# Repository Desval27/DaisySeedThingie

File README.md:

# Prototyping Carrier Board for the Daisy Seed™ 

https://electro-smith.com/products/daisy-seed

This PCB is designed to breakout all the PINs of the Daisy Seed along with additional components such as push buttons, LEDs, potentiometers, I<sup>2</sup>C, and SD card interfaces along with enough room for a typical 830 point breadboard.  

All 40 Daisy PINs are available on both sides of the board with those on the left being mirrored/inverted for additional flexibility.

[Interactive Bill of Materials (BOM)](https://github.com/Desval27/DaisySeedThingie/blob/main/bom/ibom.html)

## Ready to Order Gerber Files
- [Default](hardware/gerber_to_order/DaisySeedThingie_254.0x167.64mm_for_Default.zip)
- [Elecrow](hardware/gerber_to_order/DaisySeedThingie_254.0x167.64mm_for_Elecrow.zip)
- [FusionPCB](hardware/gerber_to_order/DaisySeedThingie_254.0x167.64mm_for_FusionPCB.zip)
- [JLCPCB](hardware/gerber_to_order/DaisySeedThingie_254.0x167.64mm_for_JLCPCB.zip)
- [PCBWay](hardware/gerber_to_order/DaisySeedThingie_254.0x167.64mm_for_PCBWay.zip)

## Status

Repository updated to Revision B.  Revision B is currently being tested.

Revsion A has several issues that are being corrected in Revision B.  Revision B is close to being finished.

- Due to footprint and learning issues no 3.5mm jacks are actually connected.  They can be hacked on the backside.
- All potentiometers are wired backwards.  CCW increases the voltage at the wiper while CW decreases it.

## Notes:
- Push buttons are connected on one side to GND to be used with input pullup GPIO pins.
- Potentiomenters are prewired on on the CW & CCW sides to +3V3 and GND.
- Audio in/out jacks are directly connected to the Seed's audio in/out pins.
   If the mono audio in jacks are used left audio in is normalized to right audio in so that they will both be available for processing by the seed if nothing is connected to right audio in.
- JST connectors are provided to breakout the Audio in/out and MIDI in/out signals to external jacks (1/4" Phono, 5-pin DIN, etc.).
- Jumpers are provided to change the configuration between TRS MIDI-A and TRS MIDI-B.  The default configuration is MIDI-A.  If MIDI-B is desired then the jumpers for MIDI-A need to be cut and those for MIDI-B bridged.

## ⚠️ Disclaimer

This project is provided **"as is"**, without warranty of any kind, express or implied,
including but not limited to the warranties of merchantability, fitness for a
particular purpose, and noninfringement.

This is a DIY electronics project intended for educational and experimental use.
Use at your own risk.

The author assumes **no responsibility or liability** for any damage, injury, or loss
resulting from the use or misuse of this design, including but not limited to:

* Damage to connected equipment (Eurorack modules, power supplies, computers, etc.)
* Incorrect assembly or wiring
* Use with incompatible voltages or signal levels
* Personal injury

### Electrical Safety

This project may interface with:

* ±12V Eurorack power rails
* External control voltages (CV)
* Digital and analog circuitry

Improper handling may result in damage or unsafe conditions.

You are responsible for:

* Verifying all connections before powering the system
* Ensuring correct polarity of power connections
* Confirming voltage ranges and signal compatibility
* Using appropriate protection circuits where necessary

### No Guarantees

Schematics, PCB layouts, and code are provided for reference only.
They may contain errors, omissions, or design flaws.

**Always review and validate the design before building or using it.**

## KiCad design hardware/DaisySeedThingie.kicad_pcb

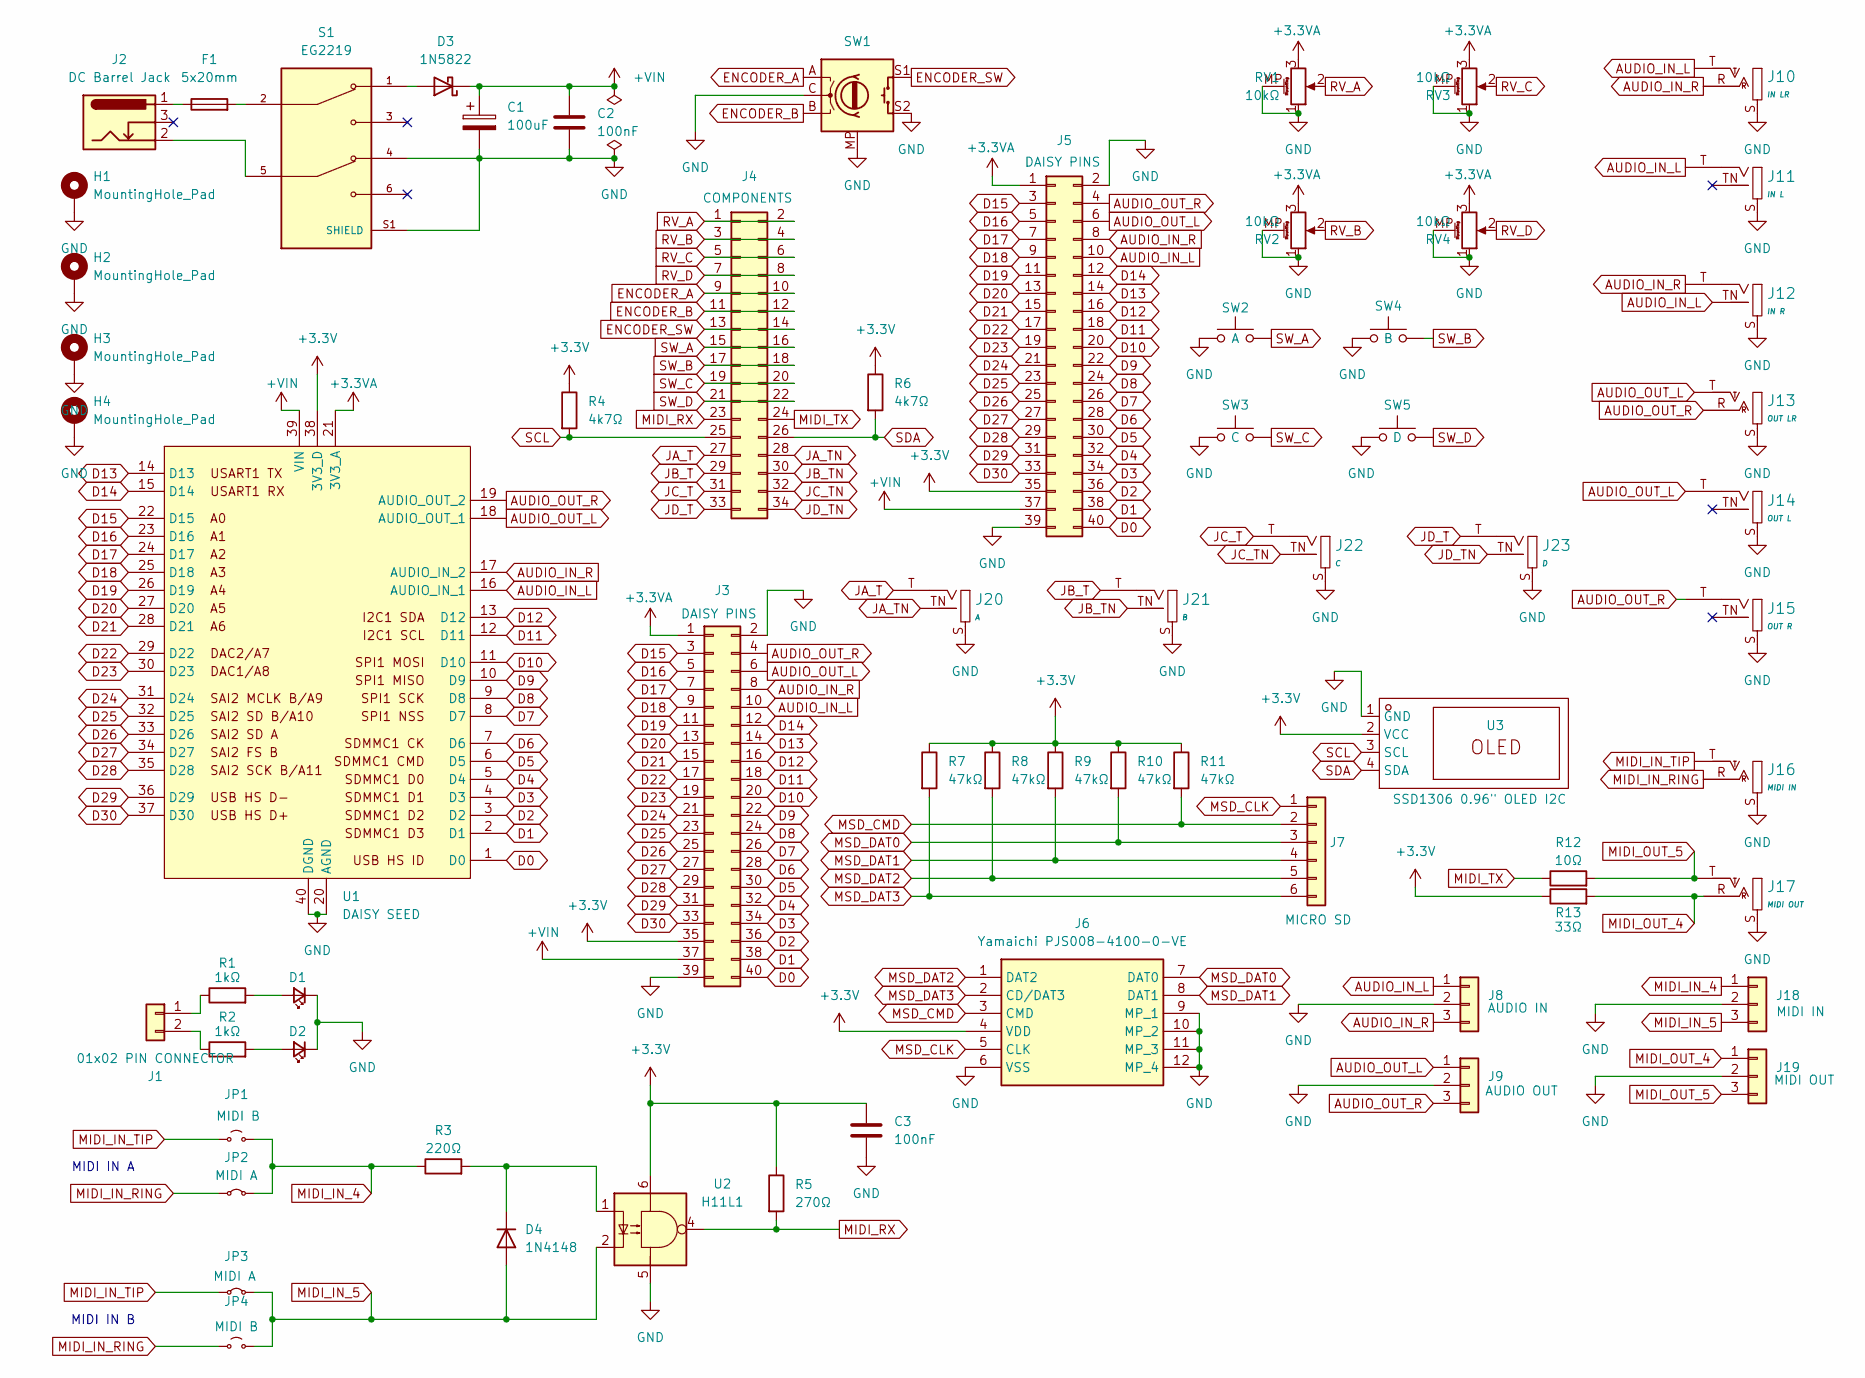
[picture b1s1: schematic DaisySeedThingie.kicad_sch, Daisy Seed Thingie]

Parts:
C1: 100uF; CP_Radial_D10.0mm_P5.00mm
C2, C3: 100nF; C_Disc_D4.3mm_W1.9mm_P5.00mm
D1, D2: RED; LED_D5.0mm_FlatTop
D3: 1N5822; D_DO-201AD_P15.24mm_Horizontal
D4: 1N4148; D_DO-35_SOD27_P7.62mm_Horizontal
F1: 5x20mm; 65600001409
H1, H2, H3, H4: MountingHole_Pad; MountingHole_3.2mm_M3_Pad
J1: 01x02 PIN CONNECTOR; PinHeader_1x02_P2.54mm_Vertical
J2: DC Barrel Jack; BarrelJack_Horizontal
J3, J5: 02x20 PIN CONNECTOR; PinHeader_2x20_P2.54mm_Vertical
J4: 02x17 PIN CONNECTOR; PinHeader_2x17_P2.54mm_Vertical
J6: Yamaichi PJS008-4100-0-VE; Yamaichi PJS00841000VE; Mouser Part Number 945-PJS008-4100-0-VE
J7: 01x06 PIN CONNECTOR; PinHeader_1x06_P2.54mm_Vertical
J8, J9, J18, J19: JST 01x03; JST_XH_B3B-XH-A_1x03_P2.50mm_Vertical
J10, J13, J16, J17: STEREO 3.5mm; Jack_3.5mm_QingPu_WQP-PJ366ST_Vertical; Part Number WQP-WQP419GR
J11, J12, J14, J15, J20, J21, J22, J23: MONO 3.5mm; Jack_3.5mm_QingPu_WQP-PJ398SM_Vertical; Part Number WQP-WQP518MA
JP1, JP4: JUMPER; Jumper_2_PTH_SMD_Combo-NO
JP2, JP3: JUMPER; Jumper_2_PTH_SMD_Combo-NC
R1, R2: 1kΩ; R_Axial_DIN0204_L3.6mm_D1.6mm_P7.62mm_Horizontal
R3: 220Ω; R_Axial_DIN0204_L3.6mm_D1.6mm_P7.62mm_Horizontal
R4, R6: 4k7Ω; R_Axial_DIN0204_L3.6mm_D1.6mm_P7.62mm_Horizontal
R5: 270Ω; R_Axial_DIN0204_L3.6mm_D1.6mm_P7.62mm_Horizontal
R7, R8, R9, R10, R11: 47kΩ; R_Axial_DIN0204_L3.6mm_D1.6mm_P7.62mm_Horizontal
R12: 10Ω; R_Axial_DIN0204_L3.6mm_D1.6mm_P7.62mm_Horizontal
R13: 33Ω; R_Axial_DIN0204_L3.6mm_D1.6mm_P7.62mm_Horizontal
RV1, RV2, RV3, RV4: 10kΩ; Potentiometer_Alps_RK09K_Single_Vertical
S1: EG2219; SW_EG2219; PARTREV B
SW1: EN11C; Rotary Encoder
SW2, SW3, SW4, SW5: SW_PUSH_6mm
U1: DAISY SEED; DAISY_SEED
U2: H11L1; DIP-6_W7.62mm_Socket_LongPads
U3: SSD1306 0.96" OLED I2C; 0.96 Inch OLED I2C Display Module; Manufacturer Part HS13L03B2C01; LCSC Part Name 1.3'1.3寸 128*64 OLED显示屏 I2C通讯 SH1106 蓝光

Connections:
+3.3V: C3.1, J3.35, J5.35, J6.4 (VDD), R4.1, R5.1, R6.1, R7.1, R8.1, R9.1, R10.1, R11.1, R13.1, U1.38 (3V3_D), U2.6, U3.2 (VCC)
+3.3VA: J3.1, J5.1, RV1.3, RV2.3, RV3.3, RV4.3, U1.21 (3V3_A)
+VIN: C1.1, C2.1, D3.1 (K), J3.37, J5.37, U1.39 (VIN)
AUDIO_IN_L: J3.10, J5.10, J8.1, J10.T (SIG), J11.T (SIG), J12.TN (SW), U1.16 (AUDIO_IN_1)
AUDIO_IN_R: J3.8, J5.8, J8.3, J10.R (SW), J12.T (SIG), U1.17 (AUDIO_IN_2)
AUDIO_OUT_L: J3.6, J5.6, J9.1, J13.T (SIG), J14.T (SIG), U1.18 (AUDIO_OUT_1)
AUDIO_OUT_R: J3.4, J5.4, J9.3, J13.R (SW), J15.T (SIG), U1.19 (AUDIO_OUT_2)
D0: J3.40, J5.40, U1.1 (D0)
D1: J3.38, J5.38, U1.2 (D1)
D2: J3.36, J5.36, U1.3 (D2)
D3: J3.34, J5.34, U1.4 (D3)
D4: J3.32, J5.32, U1.5 (D4)
D5: J3.30, J5.30, U1.6 (D5)
D6: J3.28, J5.28, U1.7 (D6)
D7: J3.26, J5.26, U1.8 (D7)
D8: J3.24, J5.24, U1.9 (D8)
D9: J3.22, J5.22, U1.10 (D9)
D10: J3.20, J5.20, U1.11 (D10)
D11: J3.18, J5.18, U1.12 (D11)
D12: J3.16, J5.16, U1.13 (D12)
D13: J3.14, J5.14, U1.14 (D13)
D14: J3.12, J5.12, U1.15 (D14)
D15: J3.3, J5.3, U1.22 (D15)
D16: J3.5, J5.5, U1.23 (D16)
D17: J3.7, J5.7, U1.24 (D17)
D18: J3.9, J5.9, U1.25 (D18)
D19: J3.11, J5.11, U1.26 (D19)
D20: J3.13, J5.13, U1.27 (D20)
D21: J3.15, J5.15, U1.28 (D21)
D22: J3.17, J5.17, U1.29 (D22)
D23: J3.19, J5.19, U1.30 (D23)
D24: J3.21, J5.21, U1.31 (D24)
D25: J3.23, J5.23, U1.32 (D25)
D26: J3.25, J5.25, U1.33 (D26)
D27: J3.27, J5.27, U1.34 (D27)
D28: J3.29, J5.29, U1.35 (D28)
D29: J3.31, J5.31, U1.36 (D29)
D30: J3.33, J5.33, U1.37 (D30)
ENCODER_A: J4.9, J4.10, SW1.A
ENCODER_B: J4.11, J4.12, SW1.B
ENCODER_SW: J4.13, J4.14, SW1.S1
GND: C1.2, C2.2, C3.2, D1.1 (K), D2.1 (K), H1.1, H2.1, H3.1, H4.1, J3.2, J3.39, J5.2, J5.39, J6.6 (VSS), J6.9 (MP_1), J6.10 (MP_2), J6.11 (MP_3), J6.12 (MP_4), J8.2, J9.2, J10.S (SHEILD), J11.S (SHEILD), J12.S (SHEILD), J13.S (SHEILD), J14.S (SHEILD), J15.S (SHEILD), J16.S (SHEILD), J17.S (SHEILD), J18.2, J19.2, J20.S (SHEILD), J21.S (SHEILD), J22.S (SHEILD), J23.S (SHEILD), RV1.1, RV1.MP (MountPin), RV2.1, RV2.MP (MountPin), RV3.1, RV3.MP (MountPin), RV4.1, RV4.MP (MountPin), S1.4, S1.S1 (SHIELD), S1.S2 (SHIELD), S1.S3 (SHIELD), S1.S4 (SHIELD), SW1.C, SW1.MP, SW1.S2, SW2.1, SW3.1, SW4.1, SW5.1, U1.20 (AGND), U1.40 (DGND), U2.5, U3.1 (GND)
JA_T: J4.27, J20.T (SIG)
JA_TN: J4.28, J20.TN (SW)
JB_T: J4.29, J21.T (SIG)
JB_TN: J4.30, J21.TN (SW)
JC_T: J4.31, J22.T (SIG)
JC_TN: J4.32, J22.TN (SW)
JD_T: J4.33, J23.T (SIG)
JD_TN: J4.34, J23.TN (SW)
MIDI_IN_4: J18.1, JP1.2 (B), JP2.2 (B), R3.1
MIDI_IN_5: D4.2 (A), J18.3, JP3.2 (B), JP4.2 (B), U2.2
MIDI_IN_RING: J16.R (SW), JP2.1 (A), JP4.1 (A)
MIDI_IN_TIP: J16.T (SIG), JP1.1 (A), JP3.1 (A)
MIDI_OUT_4: J17.R (SW), J19.1, R13.2
MIDI_OUT_5: J17.T (SIG), J19.3, R12.2
MIDI_RX: J4.23, R5.2, U2.4
MIDI_TX: J4.24, R12.1
MSD_CLK: J6.5 (CLK), J7.1
MSD_CMD: J6.3 (CMD), J7.2, R11.2
MSD_DAT0: J6.7 (DAT0), J7.3, R10.2
MSD_DAT1: J6.8 (DAT1), J7.4, R9.2
MSD_DAT2: J6.1 (DAT2), J7.5, R8.2
MSD_DAT3: J6.2 (CD/DAT3), J7.6, R7.2
unnamed: D1.2 (A), R1.2
unnamed: D2.2 (A), R2.2
unnamed: D3.2 (A), S1.1
unnamed: D4.1 (K), R3.2, U2.1
unnamed: F1.1, J2.1
unnamed: F1.2, S1.2
unnamed: J1.1, R1.1
unnamed: J1.2, R2.1
unnamed: J2.2, S1.5
RV_A: J4.1, J4.2, RV1.2
RV_B: J4.3, J4.4, RV2.2
RV_C: J4.5, J4.6, RV3.2
RV_D: J4.7, J4.8, RV4.2
SCL: J4.25, R4.2, U3.3 (SCL)
SDA: J4.26, R6.2, U3.4 (SDA)
SW_A: J4.15, J4.16, SW2.2
SW_B: J4.17, J4.18, SW4.2
SW_C: J4.19, J4.20, SW3.2
SW_D: J4.21, J4.22, SW5.2

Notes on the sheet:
MIDI IN A
MIDI IN B

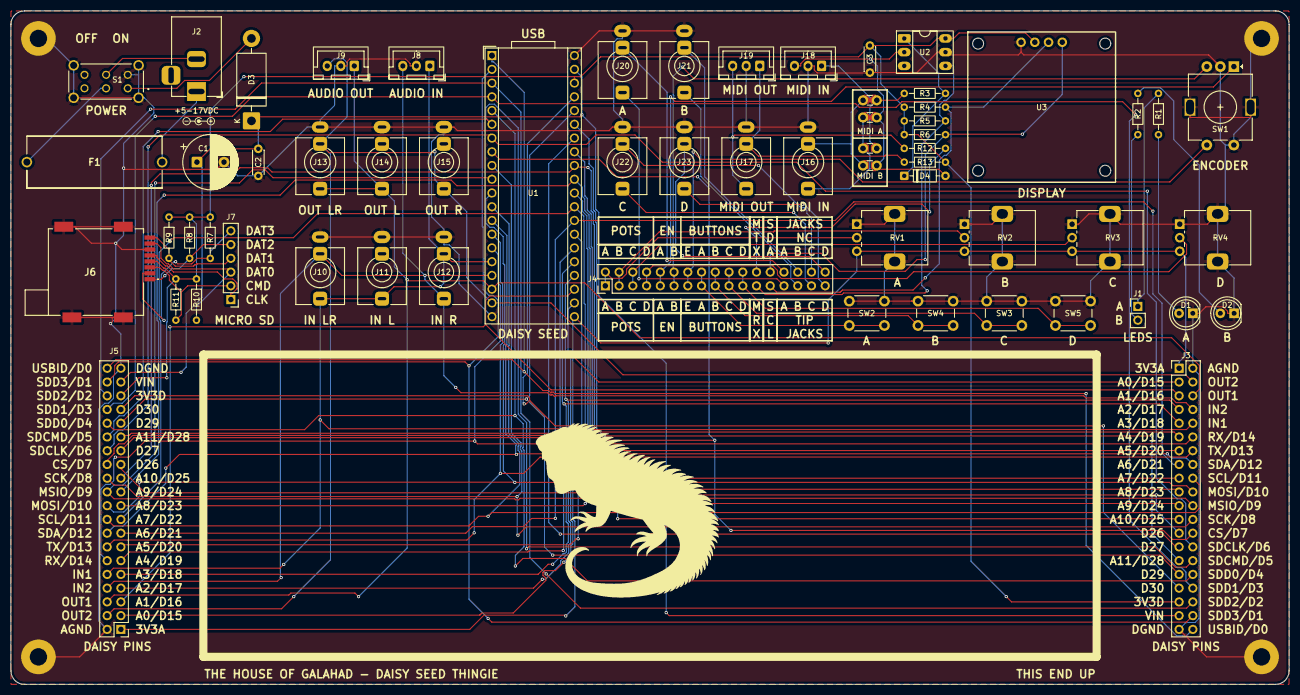
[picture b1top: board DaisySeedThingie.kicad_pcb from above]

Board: 2 copper layers, 236.2 x 124.5 mm, 65 parts (0 on the bottom side), 83 nets.

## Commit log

2026-04-06 Initial Revision B
2026-04-06 Delete gerber_to_order/DaisySeedThingie_254.0x167.64mm_for_JLCPCB.zip
    Older Revision A board with numerous errors.
2026-04-06 Enhance README formatting and add BOM link
    Updated README with improved formatting and added interactive BOM link.
2026-04-06 Fix BOM link in README.md
    Updated the link to the Interactive Bill of Materials (BOM) to point to the correct GitHub URL.
2026-04-06 Revise README with clearer notes and add disclaimer
    Updated notes for clarity and added a disclaimer section regarding project risks.
2026-04-06 Add MIT License to the project
2026-04-06 Revise disclaimer and add electrical safety information
    Updated the disclaimer section to improve clarity and added electrical safety guidelines.
2026-04-06 Rename DaisySeedThingie.kicad_pcb to hardware/DaisySeedThingie.kicad_pcb
2026-04-06 Rename DaisySeedThingie.kicad_prl to hardware/DaisySeedThingie.kicad_prl
2026-04-06 Rename DaisySeedThingie.kicad_pro to hardware/DaisySeedThingie.kicad_pro
2026-04-06 Rename DaisySeedThingie.kicad_sch to hardware/DaisySeedThingie.kicad_sch
2026-04-06 Rename DaisySeedThingie.png to hardware/DaisySeedThingie.png
2026-04-06 Fix image path for rendered PCB in README
    Updated the image path for the rendered PCB in the README.
2026-04-06 Rename DaisySeedThingie.round-tracks-config to hardware/DaisySeedThingie.round-tracks-config
2026-04-06 Restructure
2026-04-06 Restore after bad merge
2026-04-06 Added workspace
2026-04-07 Update README with Revision A and B issues
    Added notes about issues in Revision A and B.
2026-04-07 Add WIP note to README
    Added a WIP note to the README.
2026-04-09 Update README with Revision B details
    Added note about repository update to Revision B and issues with Revision A.
2026-04-09 Update README to remove WIP status
    Removed 'WIP' from the README.
2026-04-20 Refreshed Gerbers
2026-04-20 Added Gerber to Order Links
2026-04-20 Fixed typo
